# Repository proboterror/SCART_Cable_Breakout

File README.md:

# SCART RGB Cable Breakout
SCART RGB cable breakout PCB with ST662A 5V->12V converter option for automatic SCART 4:3 aspect ratio switching.

* Intended to use with common cheap plastic SCART male connectors
* Option to bypass RGB signals capacitors with solder jumpers (if your RGB source device already have them)
* Option to use separate +5V line or composite sync signal as SCART fast switch/blanking voltage source with solder jumper
* Optional 5V->12V ST662A converter for automatic 4:3 aspect ratio switch
* No sync stripper / separator option

## SCART Function Switching and Blanking
Reference from:
[fruitcake.plus.com/Sinclair/Spectrum128/SCARTCable](http://www.fruitcake.plus.com/Sinclair/Spectrum128/SCARTCable/Spectrum128SCARTCable3.htm)

|Pin|Signal|Level|
|-----|-----|-----|
|8|Function Switching|0 to 2V = TV (default option if pin unconnected).<br>5 to 8V = TV wide screen.<br>9.5 to 12V = AV mode.<br>>10k input impedance<br>[When an AV source becomes active it sets 12V on pin 8 and causes the TV to automatically switch to that SCART input. When the source stops, the signal returns to 0V and TV viewing is resumed. If a 16:9 program is present, the source raises the signal on pin 8 to only 5V.]|
|16|Blanking|75 ohm input and output impedance.<br>0V to 0.4V: TV is driven by the composite video input signal on pin 20, with transparent overlay of the Red, Green and Blue signals (default option if pin unconnected).<br>1V to 3V: TV is driven by the Red, Green, Blue signals and composite sync signal on pin 20.|
|20|Video Input<br>(Luminance Input)|1V [sync 0V - 0.3V, data 0.3V - 1V], 75 ohm input impedance<br>(1V including sync, 75 ohm output impedance)|

The FUNCTION SWITCHING signal (pin 8) is used to instruct the TV set to automatically switch to show the SCART input, and the BLANKING signal (pin 16) is used to inform the TV set whether to show a composite video or RGB signal from that SCART socket. If the BLANKING signal is left disconnected then composite video is the default AV input type. If the FUNCTION SWITCHING signal is left disconnected then the AV input must be selected manually. The table below shows the different permutations: 

|FUNCTION SWITCHING<br>(Pin 8) 	|BLANKING<br>(Pin 16) 	|TV Mode|
|-----|-----|-----|
|0V - 2V	|0V - 0.4V	|Composite Video, Manual Selection|
|0V - 2V	|1V - 3V	|RGB, Manual Selection|
|9.5V - 12V	|0V - 0.4V	|Composite Video, Automatic Selection|
|9.5V - 12V	|1V - 3V	|RGB, Automatic Selection|

## Order boards from manufacturer
Send "gerbers" folder content packed to zip archive.

## Build Notes
Be aware when ordering SMD capacitors: they should be minimal height 3.9 ~ 4.5 mm, depending on specific SCART connector. Or use A,B,C size tantalum capacitors.

180 Ohms resistor always should be soldered.

Bridge solder jumper if no separate +5V line supplied (composite sync / composite video signal used as power source for RGB selection / Status & Aspect Ratio pins).<br>
Bridge solder jumper if no 5V->12V converter option installed (connect power to Status & Aspect Ratio pins).

Cable intended to be fixed inside connector housing with nylon strap.

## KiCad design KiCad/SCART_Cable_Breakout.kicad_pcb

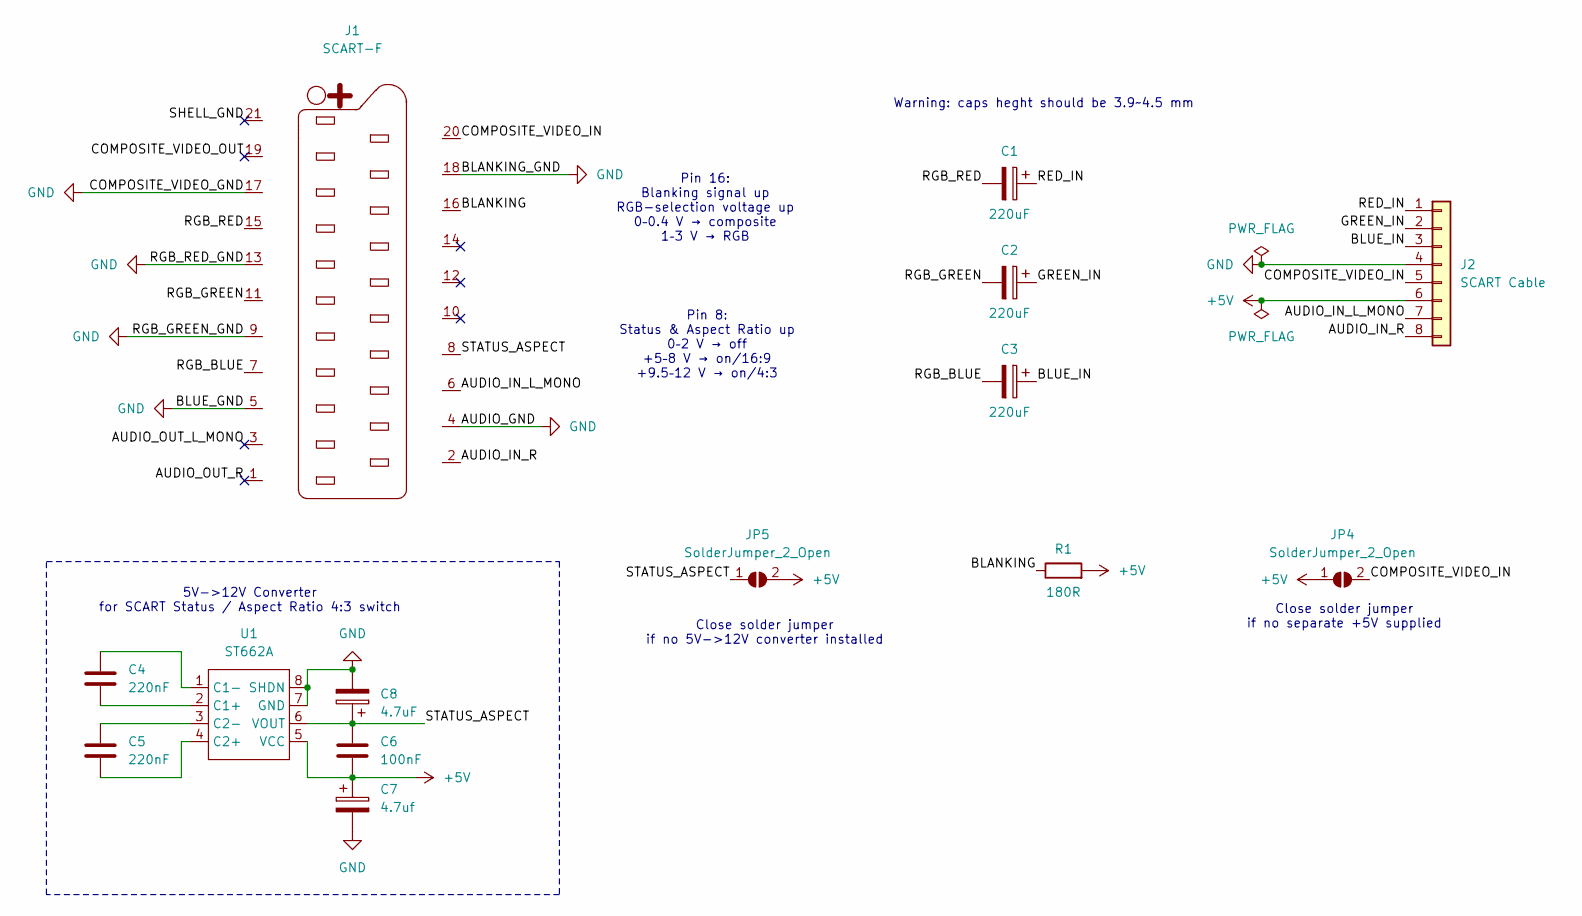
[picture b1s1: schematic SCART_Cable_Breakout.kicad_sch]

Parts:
C1, C2, C3: 220uF; CP_Elec_6.3x3.9
C4, C5: 220nF; C_0805_2012Metric_Pad1.18x1.45mm_HandSolder
C6: 100nF; C_0805_2012Metric_Pad1.18x1.45mm_HandSolder
C7: 4.7uf; CP_EIA-3528-21_Kemet-B_Pad1.50x2.35mm_HandSolder
C8: 4.7uF; CP_EIA-3528-21_Kemet-B_Pad1.50x2.35mm_HandSolder
J1: SCART-F; SCART_Cutdown
J2: SCART Cable; SCART_In
JP4, JP5: SolderJumper_2_Open; SolderJumper-2_P1.3mm_Open_RoundedPad1.0x1.5mm
R1: 180R; R_0805_2012Metric_Pad1.20x1.40mm_HandSolder
U1: ST662A; SO-8_3.9x4.9mm_P1.27mm

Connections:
+5V: C6.2, C7.1, J2.6, JP4.1 (A), JP5.2 (B), R1.2, U1.5 (VCC)
/AUDIO_IN_L_MONO: J1.6, J2.7
/AUDIO_IN_R: J1.2, J2.8
/AUDIO_OUT_L_MONO: J1.3
/AUDIO_OUT_R: J1.1
/BLANKING: J1.16, R1.1
/BLUE_IN: C3.1, J2.3
/COMPOSITE_VIDEO_IN: J1.20, J2.5, JP4.2 (B)
/COMPOSITE_VIDEO_OUT: J1.19
/GREEN_IN: C2.1, J2.2
/RED_IN: C1.1, J2.1
/RGB_BLUE: C3.2, J1.7
/RGB_GREEN: C2.2, J1.11
/RGB_RED: C1.2, J1.15
/STATUS_ASPECT: C6.1, C8.1, J1.8, JP5.1 (A), U1.6 (VOUT)
GND: C7.2, C8.2, J1.4, J1.5, J1.9, J1.13, J1.17, J1.18, J2.4, U1.7 (GND), U1.8 (SHDN)
unnamed: C4.2, U1.2 (C1+)
unnamed: C4.1, U1.1 (C1-)
unnamed: C5.2, U1.4 (C2+)
unnamed: C5.1, U1.3 (C2-)

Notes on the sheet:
Pin 16: Blanking signal up RGB-selection voltage up 0–0.4 V → composite 1–3 V → RGB
Pin 8: Status & Aspect Ratio up 0–2 V → off +5–8 V → on/16:9 +9.5–12 V → on/4:3
Close solder jumper if no separate +5V supplied
5V->12V Converter for SCART Status / Aspect Ratio 4:3 switch
Warning: caps heght should be 3.9~4.5 mm
Close solder jumper if no 5V->12V converter installed

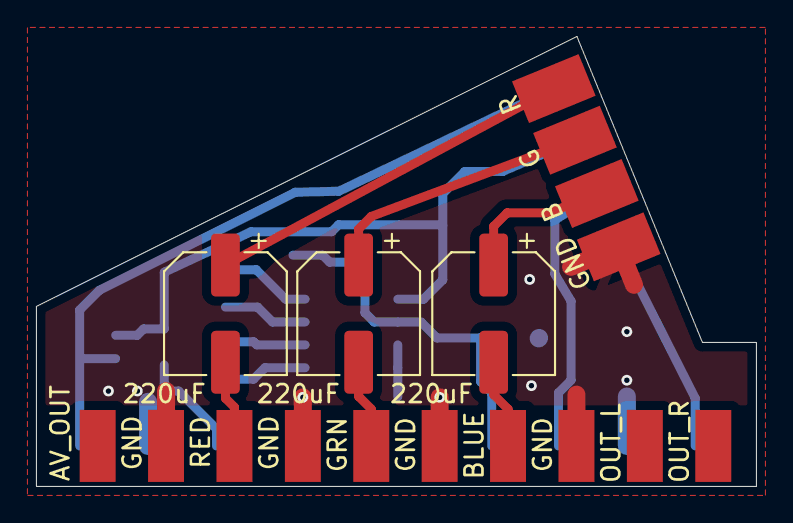
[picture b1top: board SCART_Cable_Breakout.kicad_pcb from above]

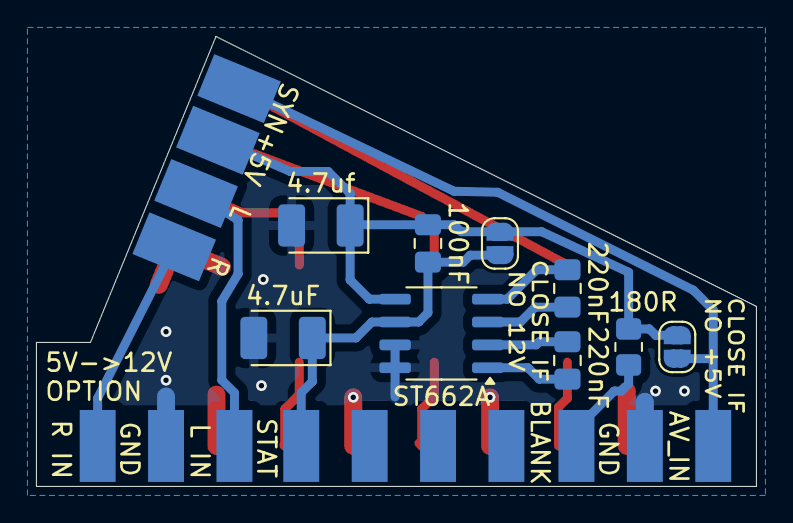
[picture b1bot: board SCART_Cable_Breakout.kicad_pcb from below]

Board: 2 copper layers, 40.0 x 25.0 mm, 14 parts (9 on the bottom side), 17 nets.

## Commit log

2025-10-17 Add kiCad 8 project.
2025-10-17 Add datasheets.
2025-10-17 Add project description.
2025-10-17 Generate fabrication gerbers output.
2025-10-17 Add PCB dimensions image to description.
2025-10-17 Add SCART Function Switching and Blanking to description.
2025-10-17 Edit silkscreen labels.
2025-10-26 Change PCB outline to match more common SCART connectors. Remove solder jumpers for RGB capacitors. 5V->12V converter: replace electrolytic capacitors with size B tantalum ones.
2025-10-26 Update project description matching PCB.
2025-10-26 Generate gerbers output. Add QR code with repository link to silkscreen.
